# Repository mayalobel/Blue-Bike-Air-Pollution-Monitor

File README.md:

Senior design project for a Blue Bike mounted air pollution monitor.

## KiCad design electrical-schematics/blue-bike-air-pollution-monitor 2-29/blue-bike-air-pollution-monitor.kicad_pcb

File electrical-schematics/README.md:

Wiring and PCB schematics created in KiCAD

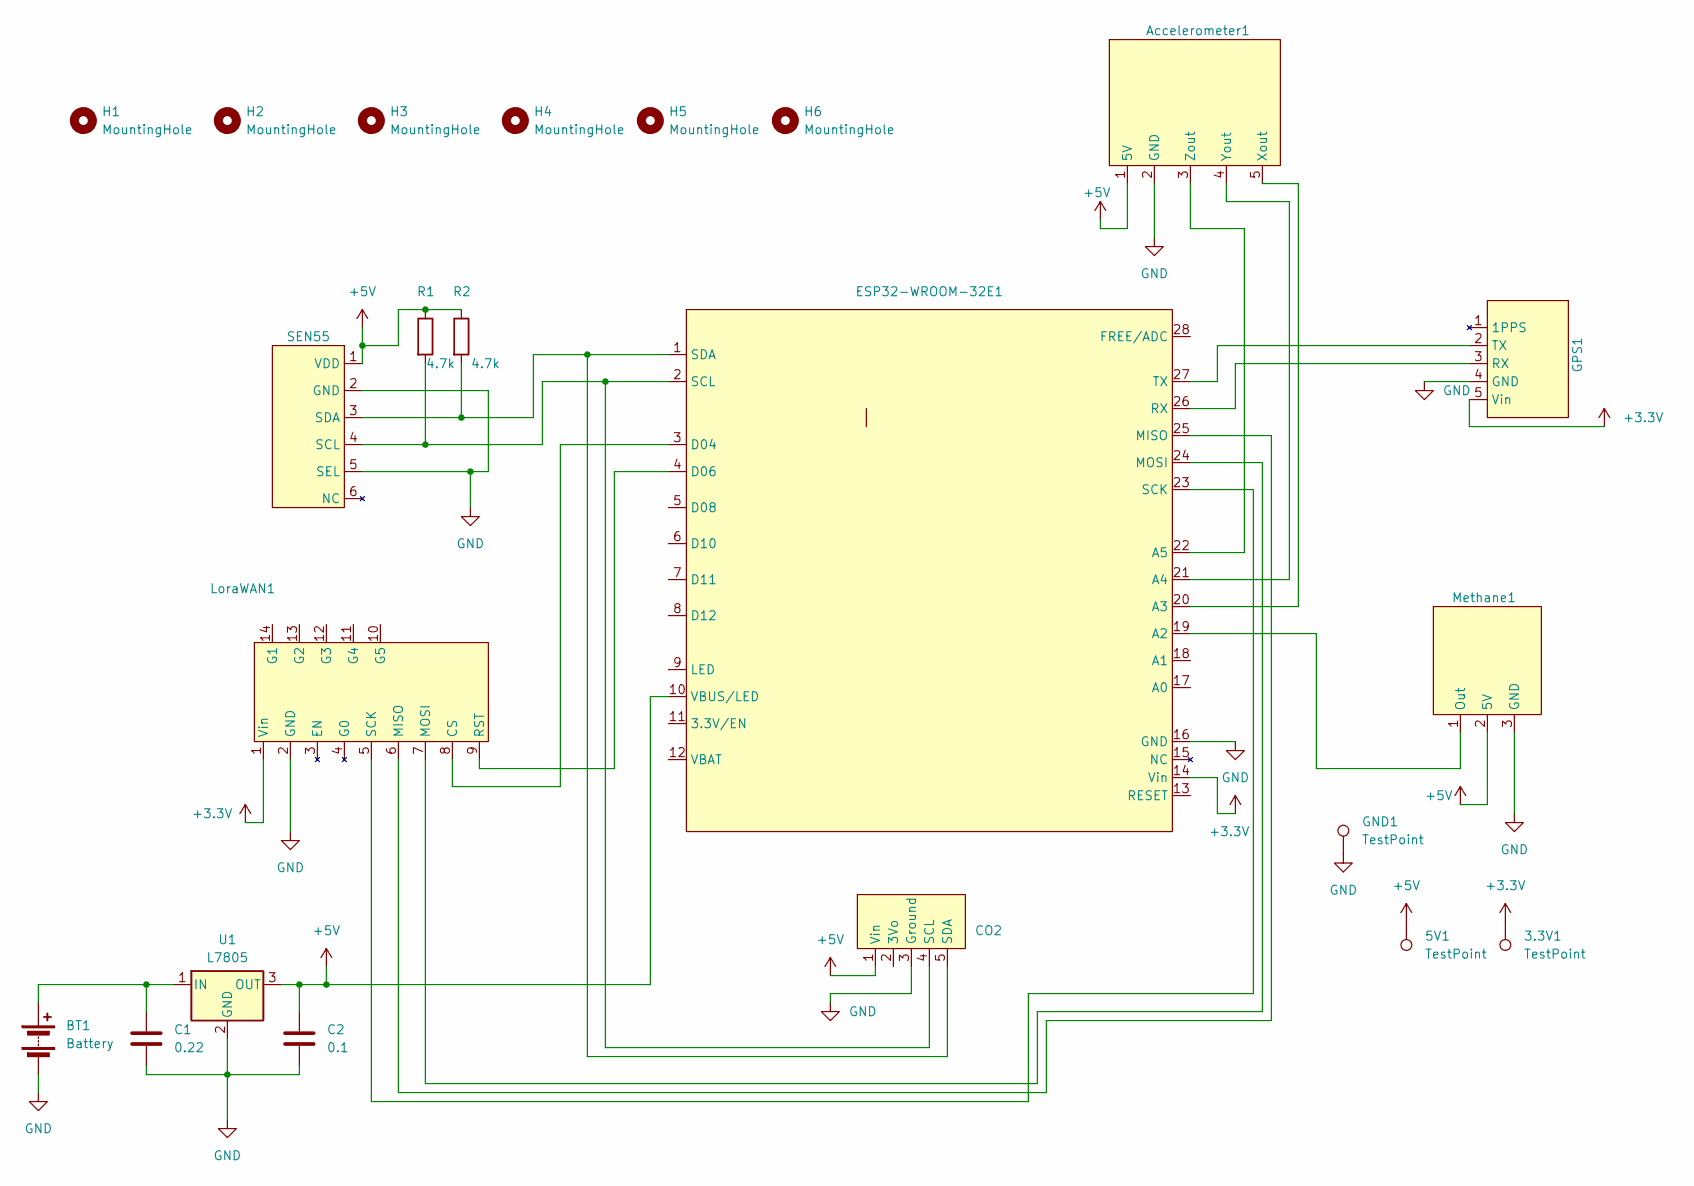
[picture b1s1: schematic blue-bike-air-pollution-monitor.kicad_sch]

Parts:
3.3V1, 5V1: TestPoint; TestPoint_Loop_D2.54mm_Drill1.5mm_Beaded
Accelerometer1: Accelerometer
BT1: Battery; PinSocket_1x02_P2.54mm_Vertical
C1: 0.22; C_Disc_D3.0mm_W2.0mm_P2.50mm
C2: 0.1; C_Disc_D3.0mm_W2.0mm_P2.50mm
CO2: CO2
ESP32-WROOM-32E1: ESP32
GND1: TestPoint; TestPoint_Loop_D2.54mm_Drill1.5mm_Beaded
GPS1: GPS
H1, H2, H3, H4, H5, H6: MountingHole; MountingHole_4.5mm_Pad
LoraWAN1: LoraWAN
Methane1: Methane
R1, R2: 4.7k; R_Axial_DIN0207_L6.3mm_D2.5mm_P7.62mm_Horizontal
SEN55: SEN55
U1: L7805; TO-220-3_Vertical

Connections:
+3.3V: 3.3V1.1, ESP32-WROOM-32E1.14 (Vin), GPS1.5 (Vin), LoraWAN1.1 (Vin)
+5V: 5V1.1, Accelerometer1.1 (5V), C2.1, CO2.1 (Vin), ESP32-WROOM-32E1.10 (VBUS/LED), Methane1.2 (5V), R1.1, R2.1, SEN55.1 (VDD), U1.3 (OUT)
GND: Accelerometer1.2 (GND), BT1.2 (-), C1.2, C2.2, CO2.3 (Ground), ESP32-WROOM-32E1.16 (GND), GND1.1, GPS1.4 (GND), LoraWAN1.2 (GND), Methane1.3 (GND), SEN55.2 (GND), SEN55.5 (SEL), U1.2 (GND)
unnamed: Accelerometer1.5 (Xout), ESP32-WROOM-32E1.20 (A3)
unnamed: Accelerometer1.4 (Yout), ESP32-WROOM-32E1.21 (A4)
unnamed: Accelerometer1.3 (Zout), ESP32-WROOM-32E1.22 (A5)
unnamed: BT1.1 (+), C1.1, U1.1 (IN)
unnamed: CO2.4 (SCL), ESP32-WROOM-32E1.2 (SCL), R1.2, SEN55.4 (SCL)
unnamed: CO2.5 (SDA), ESP32-WROOM-32E1.1 (SDA), R2.2, SEN55.3 (SDA)
unnamed: ESP32-WROOM-32E1.19 (A2), Methane1.1 (Out)
unnamed: ESP32-WROOM-32E1.3 (D04), LoraWAN1.8 (CS)
unnamed: ESP32-WROOM-32E1.4 (D06), LoraWAN1.9 (RST)
unnamed: ESP32-WROOM-32E1.25 (MISO), LoraWAN1.6 (MISO)
unnamed: ESP32-WROOM-32E1.24 (MOSI), LoraWAN1.7 (MOSI)
unnamed: ESP32-WROOM-32E1.26 (RX), GPS1.3 (RX)
unnamed: ESP32-WROOM-32E1.23 (SCK), LoraWAN1.5 (SCK)
unnamed: ESP32-WROOM-32E1.27 (TX), GPS1.2 (TX)

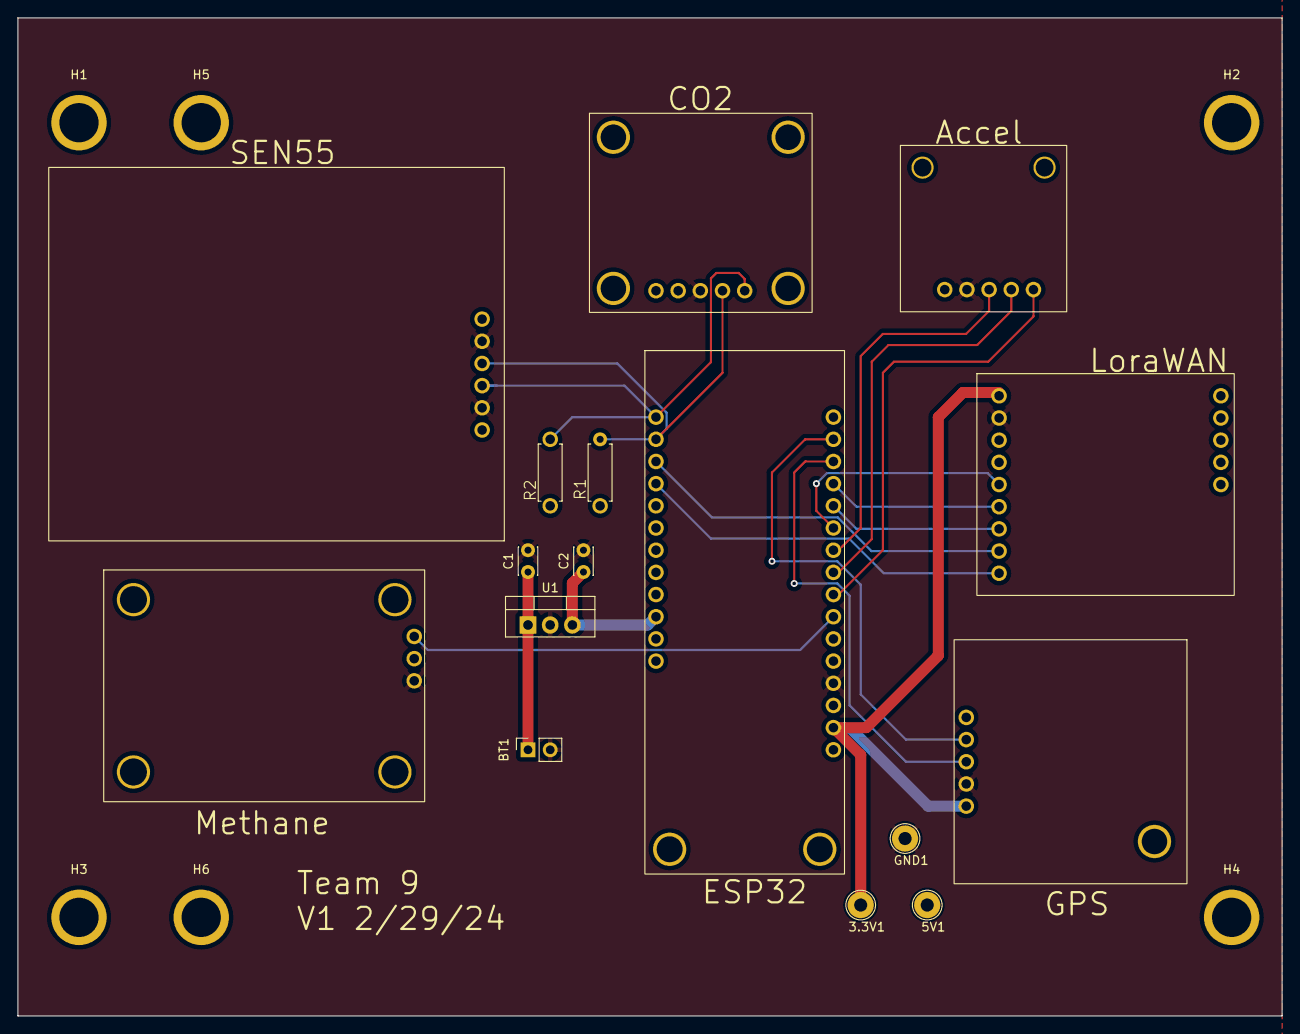
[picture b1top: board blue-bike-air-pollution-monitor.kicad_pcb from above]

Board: 2 copper layers, 144.8 x 114.3 mm, 22 parts (0 on the bottom side), 17 nets.

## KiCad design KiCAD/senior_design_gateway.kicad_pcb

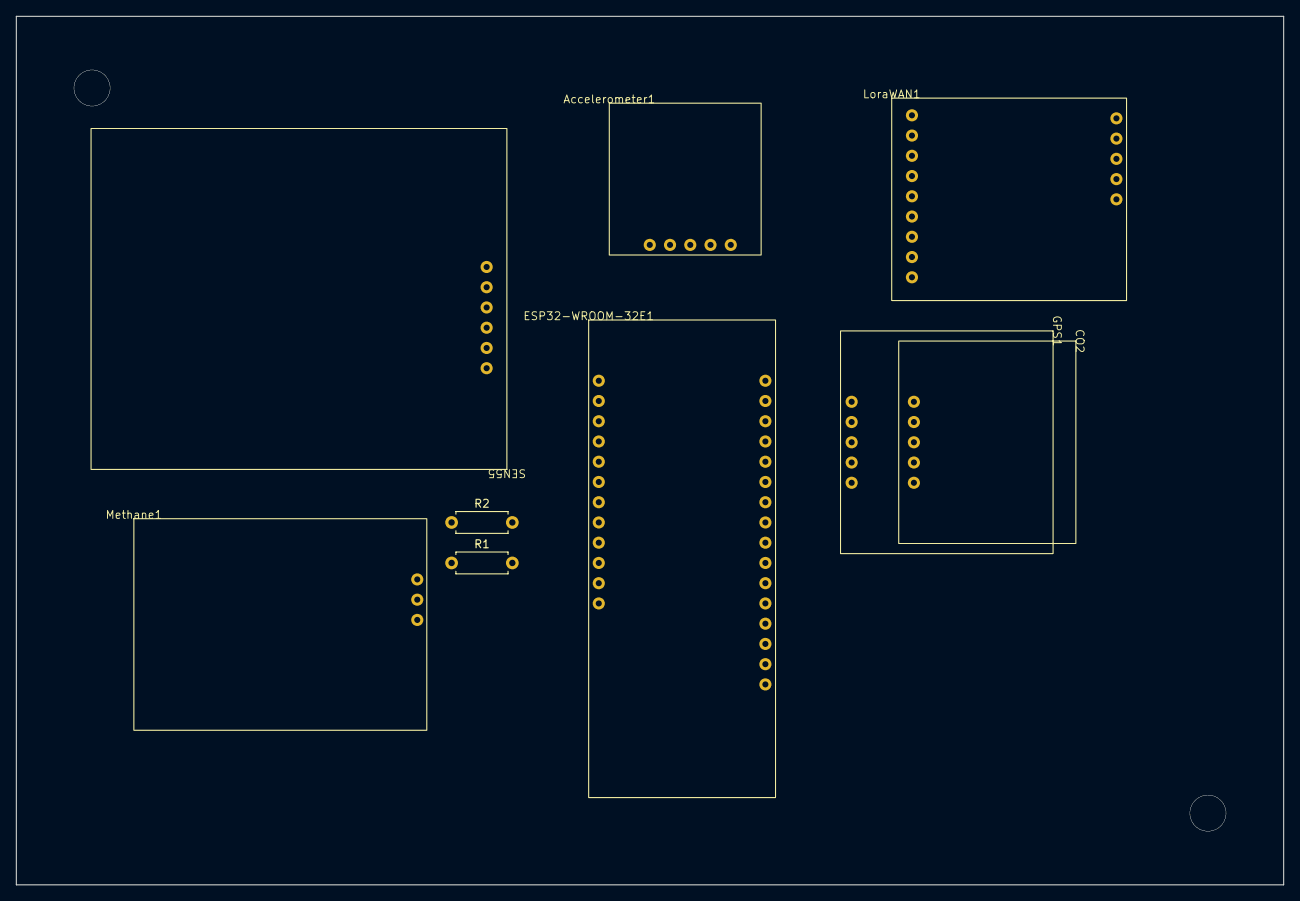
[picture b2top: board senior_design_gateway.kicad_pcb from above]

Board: 2 copper layers, 159.0 x 109.0 mm, 9 parts (0 on the bottom side), 5 nets, no tracks yet.

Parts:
Accelerometer1: Accelerometer
CO2: CO2
ESP32-WROOM-32E1: ESP32
GPS1: GPS
LoraWAN1: LoraWAN
Methane1: Methane
R1, R2: R; R_Axial_DIN0207_L6.3mm_D2.5mm_P7.62mm_Horizontal
SEN55: SEN55

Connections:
+3.3V: GPS1.5 (Vin), LoraWAN1.1 (Vin)
+5V: Accelerometer1.1 (5V), CO2.1 (Vin), Methane1.2 (5V), R1.1, R2.1, SEN55.1 (VDD)
GND: Accelerometer1.2 (GND), CO2.3 (Ground), GPS1.2 (GND), LoraWAN1.2 (GND), Methane1.3 (GND), SEN55.2 (GND), SEN55.5 (SEL)
unnamed: CO2.4 (SCL), R1.2, SEN55.4 (SCL)
unnamed: CO2.5 (SDA), R2.2, SEN55.3 (SDA)

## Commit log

2024-02-21 edits by Eric during 2/21 meeting
2024-02-25 Add files via upload
    2/25 KiCAD files
2024-02-28 Team 9 changes as of 2/27
2024-02-29 Team 9 changes as of 2/28
2024-03-01 Team 9 changes as of 2/29
    Updated mounting hole pattern
2024-03-23 Team 9 changes as of 3/23
2024-03-26 Rename README.md to KiCAD/README.md
2024-03-26 Rename README.md~ to KiCAD/README.md~
2024-04-04 Upload Arduino Code via File Upload
    Arduino Code for all sensors and serial monitor output
2024-04-17 Add files via upload
    LoRaWAN
2024-04-18 Data collected by monitor
2024-04-29 Data files collected by Team 9
2024-04-29 MassDEP data files
